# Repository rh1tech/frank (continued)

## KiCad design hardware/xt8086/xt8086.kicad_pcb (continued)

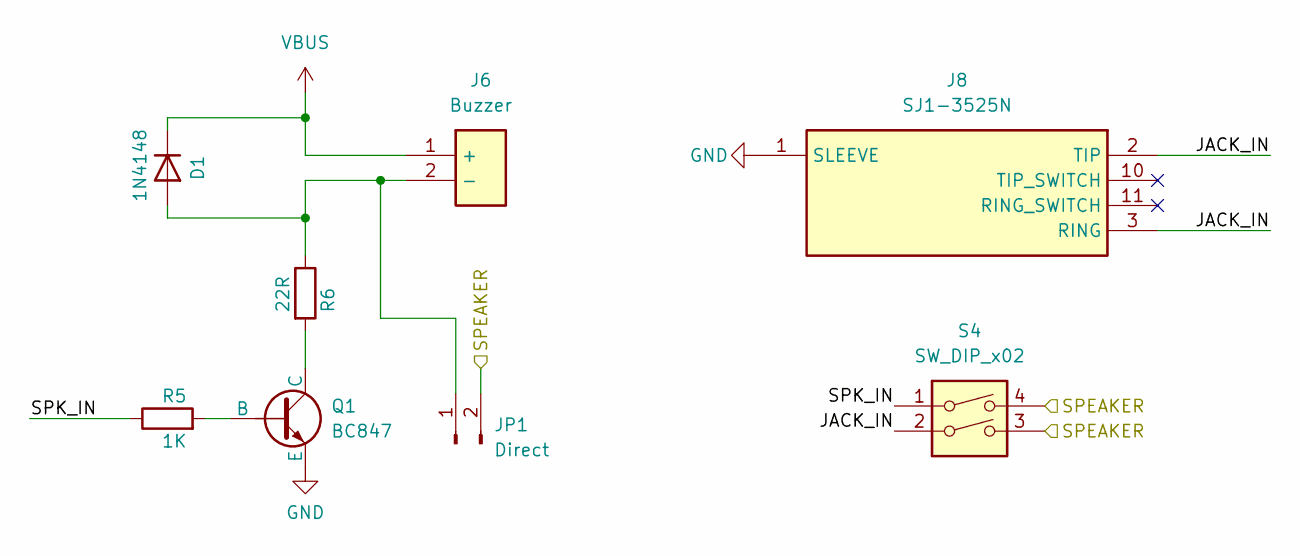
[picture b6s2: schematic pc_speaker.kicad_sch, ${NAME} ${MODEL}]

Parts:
D1: 1N4148; D_SOD-323
J6: Buzzer; Buzzer_12x8.5RM6.5; Mouser Part Number 490-CMT-7525-80SMTTR
J8: SJ1-3525N; AudioJack_3.5mm_SJ1-3525N; Mouser Part Number 490-SJ1-3525N
JP1: Direct; SolderJumper-2_P1.3mm_Open_Pad1.0x1.5mm
Q1: BC847; SOT-23
R5: 1K; R_0805_2012Metric
R6: 22R; R_0805_2012Metric
S4: SW_DIP_x02; SW_DIP_SPSTx02_Slide_9.78x7.26mm_W7.62mm_P2.54mm

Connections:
/Audio/JACK_IN: J8.2 (TIP), J8.3 (RING), S4.2
/Audio/SPEAKER: JP1.2, S4.3, S4.4; also elsewhere on the board
/Audio/SPK_IN: R5.1, S4.1
GND: J8.1 (SLEEVE), Q1.3 (E); also elsewhere on the board
unnamed: D1.2 (A), J6.2 (-), JP1.1, R6.1
unnamed: Q1.2 (B), R5.2
unnamed: Q1.1 (C), R6.2
VBUS: D1.1 (K), J6.1 (+); also elsewhere on the board

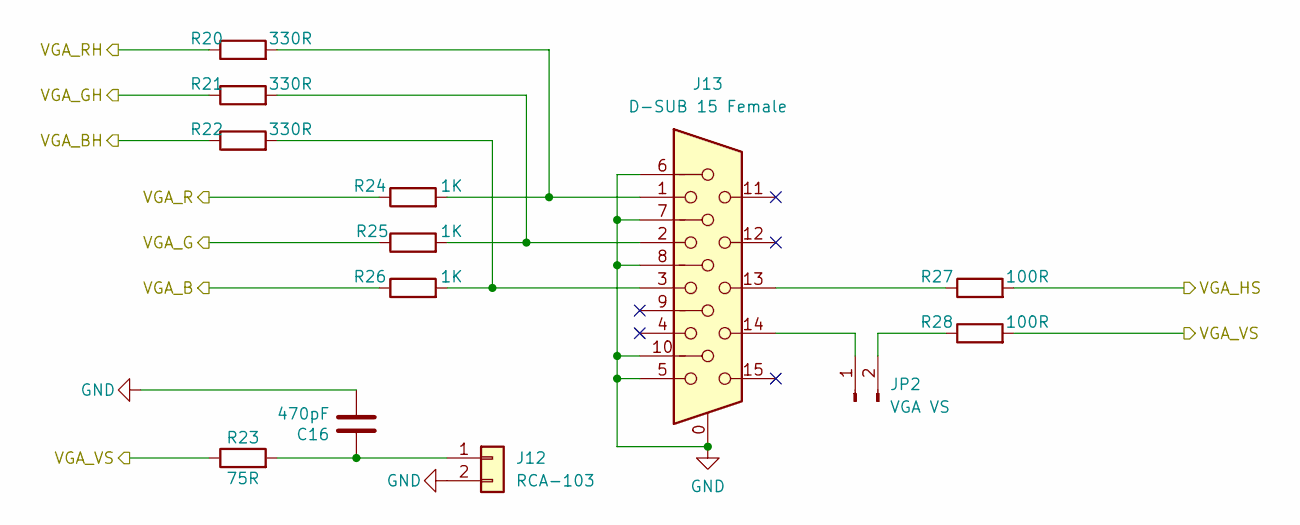
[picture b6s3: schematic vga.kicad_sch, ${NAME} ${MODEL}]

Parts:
C16: 470pF; C_0805_2012Metric
J12: RCA-103; BarrelJack_RCJ-012
J13: D-SUB 15 Female; DSUB-15_Female
JP2: VGA VS; PinHeader_1x02_P2.54mm
R20, R21, R22: 330R; R_0805_2012Metric
R23: 75R; R_0805_2012Metric
R24, R25, R26: 1K; R_0805_2012Metric
R27, R28: 100R; R_0805_2012Metric

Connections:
/PGA2350/GP30: R26.1; also elsewhere on the board
/PGA2350/GP31: R22.1; also elsewhere on the board
/PGA2350/GP32: R25.1; also elsewhere on the board
/PGA2350/GP33: R21.1; also elsewhere on the board
/PGA2350/GP34: R24.1; also elsewhere on the board
/PGA2350/GP35: R20.1; also elsewhere on the board
/PGA2350/GP36: R27.2; also elsewhere on the board
/PGA2350/GP37: R23.1, R28.2; also elsewhere on the board
GND: C16.2, J12.2, J13.0, J13.5, J13.6, J13.7, J13.8, J13.10; also elsewhere on the board
unnamed: C16.1, J12.1, R23.2
unnamed: J13.1, R20.2, R24.2
unnamed: J13.2, R21.2, R25.2
unnamed: J13.3, R22.2, R26.2
unnamed: J13.13, R27.1
unnamed: J13.14, JP2.1
unnamed: JP2.2, R28.1

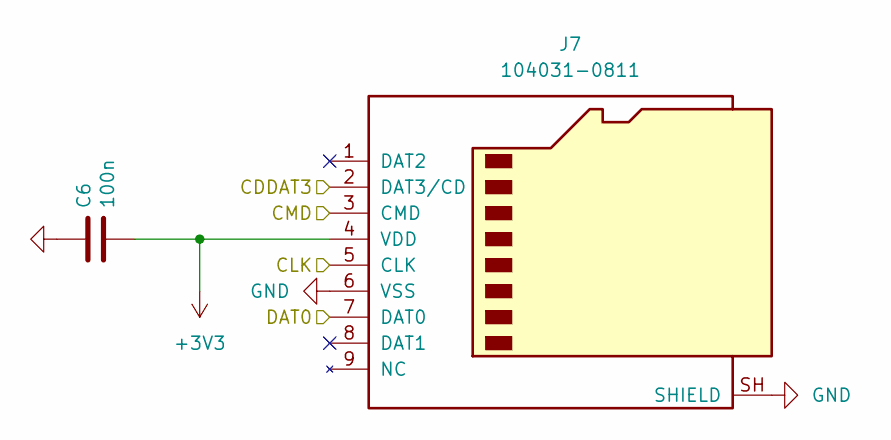
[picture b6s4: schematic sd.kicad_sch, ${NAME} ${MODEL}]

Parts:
C6: 100n; C_0805_2012Metric
J7: 104031-0811; MicroSD_SMD_Long

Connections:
+3V3: C6.2, J7.4 (VDD); also elsewhere on the board
/Micro SD/CDDAT3: J7.2 (DAT3/CD); also elsewhere on the board
/Micro SD/CLK: J7.5 (CLK); also elsewhere on the board
/Micro SD/CMD: J7.3 (CMD); also elsewhere on the board
/Micro SD/DAT0: J7.7 (DAT0); also elsewhere on the board
GND: C6.1, J7.6 (VSS), J7.SH (SHIELD); also elsewhere on the board

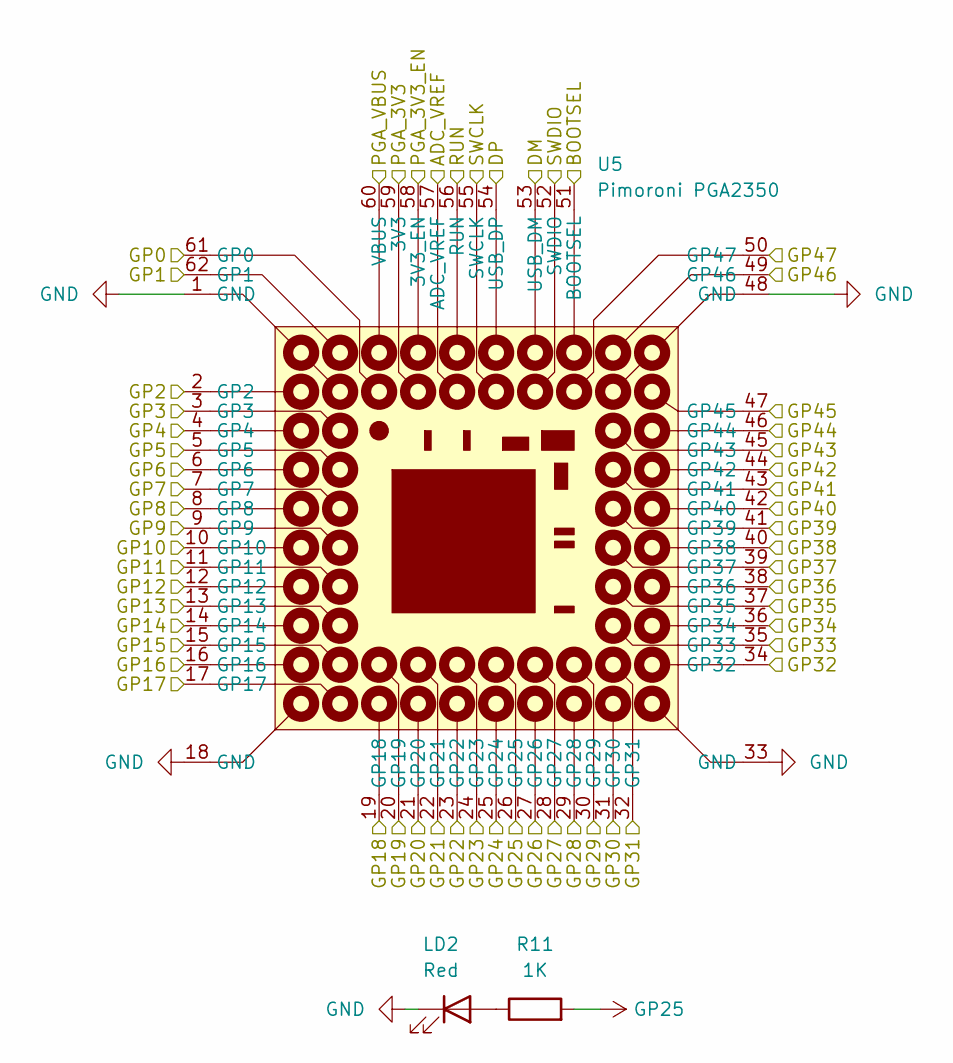
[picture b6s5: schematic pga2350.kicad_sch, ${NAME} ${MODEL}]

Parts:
LD2: Red; LED_0805_2012Metric_Pad1.15x1.40mm_HandSolder
R11: 1K; R_0805_2012Metric
U5: Pimoroni PGA2350; PGA2350

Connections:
+3V3: U5.59 (3V3); also elsewhere on the board
/A16/GP16: U5.16 (GP16); also elsewhere on the board
/A17/GP17: U5.17 (GP17); also elsewhere on the board
/A18/GP18: U5.19 (GP18); also elsewhere on the board
/A19/GP19: U5.20 (GP19); also elsewhere on the board
/AD0/GP0: U5.61 (GP0); also elsewhere on the board
/AD1/GP1: U5.62 (GP1); also elsewhere on the board
/AD2/GP2: U5.2 (GP2); also elsewhere on the board
/AD3/GP3: U5.3 (GP3); also elsewhere on the board
/AD4/GP4: U5.4 (GP4); also elsewhere on the board
/AD5/GP5: U5.5 (GP5); also elsewhere on the board
/AD6/GP6: U5.6 (GP6); also elsewhere on the board
/AD7/GP7: U5.7 (GP7); also elsewhere on the board
/AD8/GP8: U5.8 (GP8); also elsewhere on the board
/AD9/GP9: U5.9 (GP9); also elsewhere on the board
/AD10/GP10: U5.10 (GP10); also elsewhere on the board
/AD11/GP11: U5.11 (GP11); also elsewhere on the board
/AD12/GP12: U5.12 (GP12); also elsewhere on the board
/AD13/GP13: U5.13 (GP13); also elsewhere on the board
/AD14/GP14: U5.14 (GP14); also elsewhere on the board
/AD15/GP15: U5.15 (GP15); also elsewhere on the board
/ALE/GP20: U5.21 (GP20); also elsewhere on the board
/Audio/SPEAKER: U5.49 (GP46); also elsewhere on the board
/BOOTSEL: U5.51 (BOOTSEL); also elsewhere on the board
/CLK/GP29: U5.30 (GP29); also elsewhere on the board
/GP27: U5.28 (GP27); also elsewhere on the board
/INTA/GP23: U5.24 (GP23); also elsewhere on the board
/INTR/GP26: U5.27 (GP26); also elsewhere on the board
/MIO/GP24: U5.25 (GP24); also elsewhere on the board
/Micro SD/CDDAT3: U5.43 (GP41); also elsewhere on the board
/Micro SD/CLK: U5.44 (GP42); also elsewhere on the board
/Micro SD/CMD: U5.45 (GP43); also elsewhere on the board
/Micro SD/DAT0: U5.42 (GP40); also elsewhere on the board
/PGA2350/ADC_VREF: U5.57 (ADC_VREF)
/PGA2350/DM: U5.53 (USB_DM); also elsewhere on the board
/PGA2350/DP: U5.54 (USB_DP); also elsewhere on the board
/PGA2350/GP30: U5.31 (GP30); also elsewhere on the board
/PGA2350/GP31: U5.32 (GP31); also elsewhere on the board
/PGA2350/GP32: U5.34 (GP32); also elsewhere on the board
/PGA2350/GP33: U5.35 (GP33); also elsewhere on the board
/PGA2350/GP34: U5.36 (GP34); also elsewhere on the board
/PGA2350/GP35: U5.37 (GP35); also elsewhere on the board
/PGA2350/GP36: U5.38 (GP36); also elsewhere on the board
/PGA2350/GP37: U5.39 (GP37); also elsewhere on the board
/PGA2350/GP38: U5.40 (GP38)
/PGA2350/GP39: U5.41 (GP39)
/PGA2350/GP47: U5.50 (GP47)
/PGA2350/PGA_3V3_EN: U5.58 (3V3_EN)
/RD/GP21: U5.22 (GP21); also elsewhere on the board
/RESET/GP28: U5.29 (GP28); also elsewhere on the board
/RUN: U5.56 (RUN); also elsewhere on the board
/SWCLK: U5.55 (SWCLK); also elsewhere on the board
/SWDIO: U5.52 (SWDIO); also elsewhere on the board
/UART0_RX: U5.47 (GP45); also elsewhere on the board
/UART0_TX: U5.46 (GP44); also elsewhere on the board
/WR/GP22: U5.23 (GP22); also elsewhere on the board
GND: LD2.1 (K), U5.1 (GND), U5.18 (GND), U5.33 (GND), U5.48 (GND); also elsewhere on the board
GP25: R11.2, U5.26 (GP25); also elsewhere on the board
unnamed: LD2.2 (A), R11.1
VBUS: U5.60 (VBUS); also elsewhere on the board

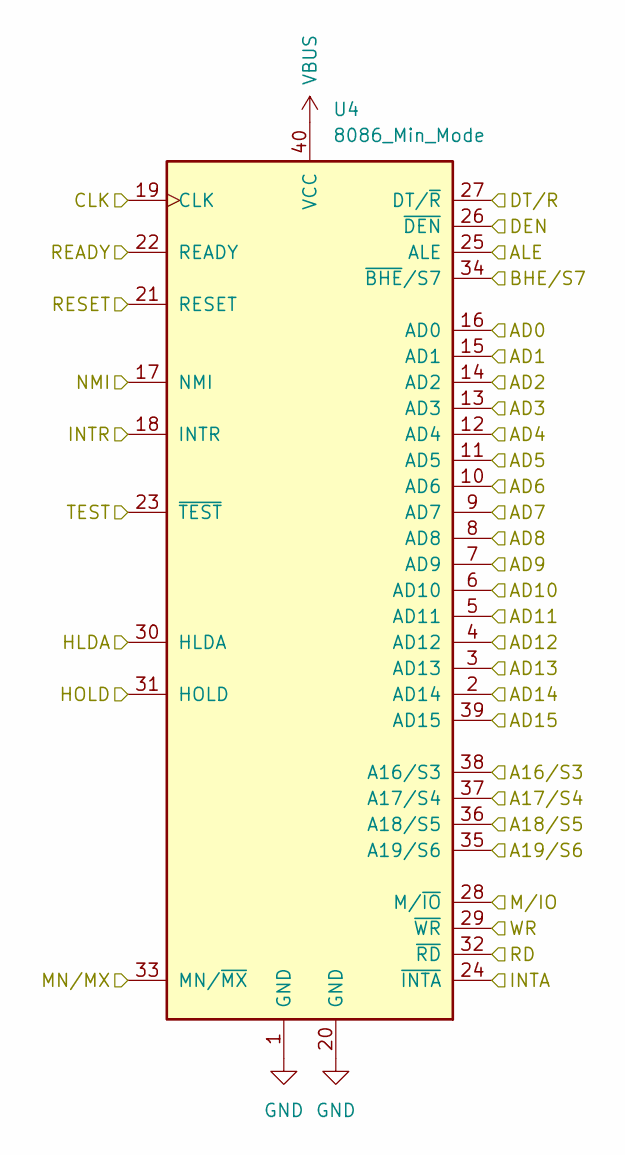
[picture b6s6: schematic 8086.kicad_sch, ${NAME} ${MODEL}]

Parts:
U4: 8086_Min_Mode; DIP-40_W15.24mm

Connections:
/A16/GP16: U4.38 (A16/S3); also elsewhere on the board
/A17/GP17: U4.37 (A17/S4); also elsewhere on the board
/A18/GP18: U4.36 (A18/S5); also elsewhere on the board
/A19/GP19: U4.35 (A19/S6); also elsewhere on the board
/AD0/GP0: U4.16 (AD0); also elsewhere on the board
/AD1/GP1: U4.15 (AD1); also elsewhere on the board
/AD2/GP2: U4.14 (AD2); also elsewhere on the board
/AD3/GP3: U4.13 (AD3); also elsewhere on the board
/AD4/GP4: U4.12 (AD4); also elsewhere on the board
/AD5/GP5: U4.11 (AD5); also elsewhere on the board
/AD6/GP6: U4.10 (AD6); also elsewhere on the board
/AD7/GP7: U4.9 (AD7); also elsewhere on the board
/AD8/GP8: U4.8 (AD8); also elsewhere on the board
/AD9/GP9: U4.7 (AD9); also elsewhere on the board
/AD10/GP10: U4.6 (AD10); also elsewhere on the board
/AD11/GP11: U4.5 (AD11); also elsewhere on the board
/AD12/GP12: U4.4 (AD12); also elsewhere on the board
/AD13/GP13: U4.3 (AD13); also elsewhere on the board
/AD14/GP14: U4.2 (AD14); also elsewhere on the board
/AD15/GP15: U4.39 (AD15); also elsewhere on the board
/ALE/GP20: U4.25 (ALE); also elsewhere on the board
/CLK/GP29: U4.19 (CLK); also elsewhere on the board
/DEN: U4.26 (~DEN); also elsewhere on the board
/DT/R: U4.27 (DT/~R); also elsewhere on the board
/HLDA: U4.30 (HLDA); also elsewhere on the board
/INTA/GP23: U4.24 (~INTA); also elsewhere on the board
/INTR/GP26: U4.18 (INTR); also elsewhere on the board
/MIO/GP24: U4.28 (M/~IO); also elsewhere on the board
/MN/MX: U4.33 (MN/~MX); also elsewhere on the board
/RD/GP21: U4.32 (~RD); also elsewhere on the board
/READY: U4.22 (READY); also elsewhere on the board
/RESET/GP28: U4.21 (RESET); also elsewhere on the board
/TEST: U4.23 (~TEST); also elsewhere on the board
/WR/GP22: U4.29 (~WR); also elsewhere on the board
GND: U4.1 (GND), U4.17 (NMI), U4.20 (GND), U4.31 (HOLD); also elsewhere on the board
GP25: U4.34 (~BHE/S7); also elsewhere on the board
VBUS: U4.40 (VCC); also elsewhere on the board

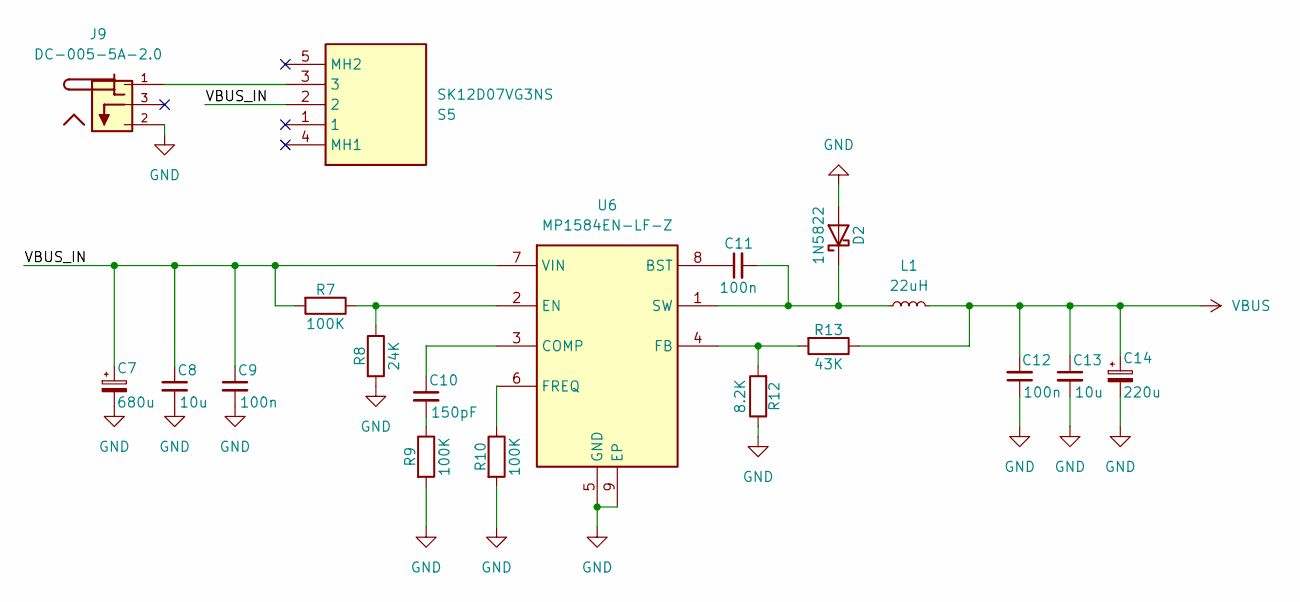
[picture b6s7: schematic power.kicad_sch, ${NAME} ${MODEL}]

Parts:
C7: 680u; C_Radial_D8.0mm_P3.50mm
C8, C13: 10u; C_0805_2012Metric
C9, C11, C12: 100n; C_0805_2012Metric
C10: 150pF; R_0805_2012Metric
C14: 220u; C_Radial_D6.3mm_P2.50mm
D2: 1N5822; D_SMA
J9: DC-005-5A-2.0; BarrelJack_DC-005; PARTREV A0
L1: 22uH; L_Radial_D9.5mm_P5.00mm_Fastron_07HVP
R7, R9, R10: 100K; R_0805_2012Metric
R8: 24K; R_0805_2012Metric
R12: 8.2K; R_0805_2012Metric
R13: 43K; R_0805_2012Metric
S5: SK12D07VG3NS; Switch_Slide_SK12D07VG3NS; Mouser Part Number 611-SK12D07VG3NS
U6: MP1584EN-LF-Z; SOIC-9_P1.27mm; Mouser Part Number 946-MP1584ENLFZ

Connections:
/Power/VBUS_IN: C7.1, C8.1, C9.1, R7.2, S5.2, U6.7 (VIN)
GND: C7.2, C8.2, C9.2, C12.1, C13.2, C14.2, D2.2 (A), J9.2, R8.2, R9.2, R10.2, R12.1, U6.5 (GND), U6.9 (EP); also elsewhere on the board
unnamed: C10.2, R9.1
unnamed: C11.2, D2.1 (K), L1.1, U6.1 (SW)
unnamed: J9.1, S5.3
unnamed: C11.1, U6.8 (BST)
unnamed: C10.1, U6.3 (COMP)
unnamed: R7.1, R8.1, U6.2 (EN)
unnamed: R12.2, R13.2, U6.4 (FB)
unnamed: R10.1, U6.6 (FREQ)
VBUS: C12.2, C13.1, C14.1, L1.2, R13.1; also elsewhere on the board

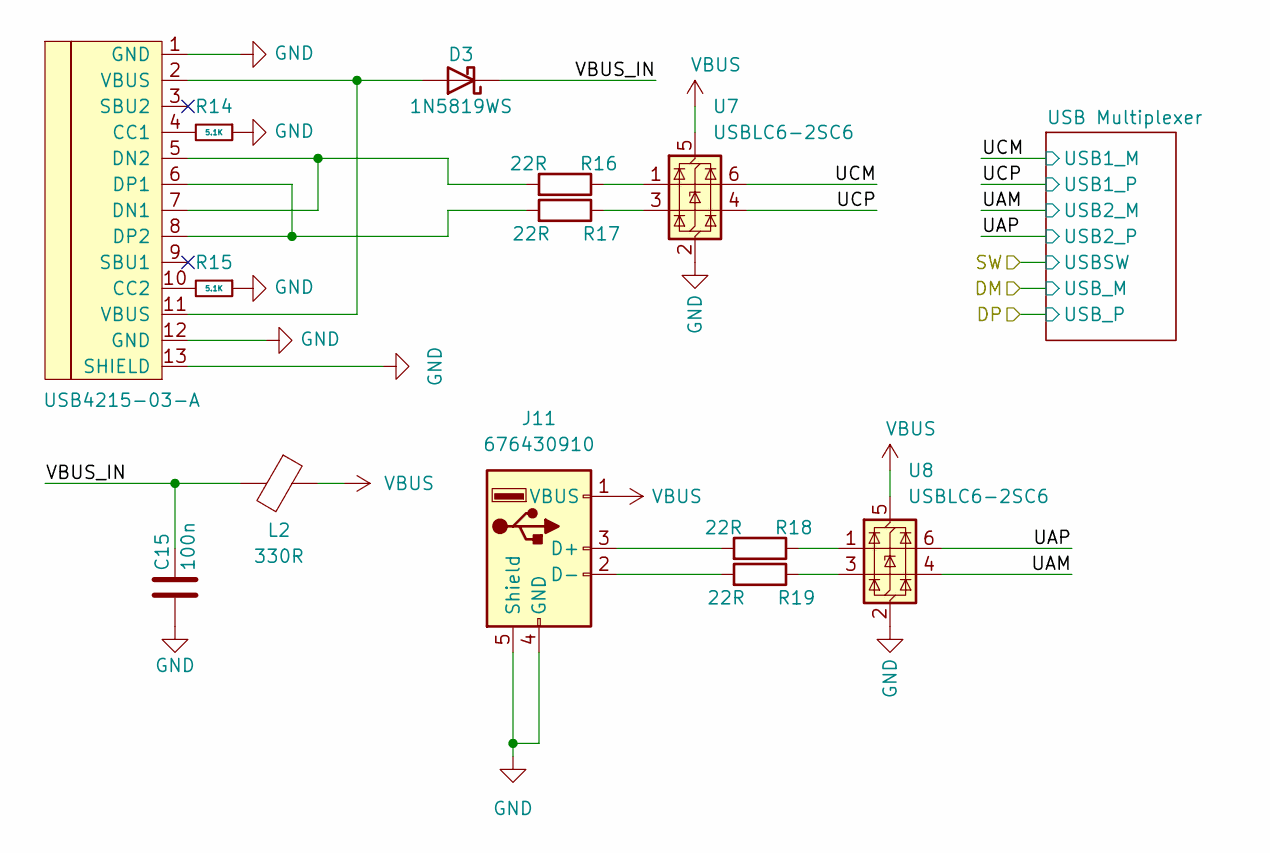
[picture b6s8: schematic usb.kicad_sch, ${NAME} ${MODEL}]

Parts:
C15: 100n; C_0805_2012Metric
D3: 1N5819WS; D_SOD-323
J10: USB4215-03-A; USB_C_Receptacle; LCSC C165948
J11: 676430910; USB_A_Single
L2: 330R; R_0805_2012Metric
R14, R15: 5.1K; R_0805_2012Metric
R16, R17, R18, R19: 22R; R_0805_2012Metric
U7, U8: USBLC6-2SC6; SOT-23-6

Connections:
/USB/UAM: U8.4 (I/O2); also elsewhere on the board
/USB/UAP: U8.6 (I/O1); also elsewhere on the board
/USB/UCM: U7.6 (I/O1); also elsewhere on the board
/USB/UCP: U7.4 (I/O2); also elsewhere on the board
/USB/VBUS_IN: C15.1, D3.1 (K), L2.2
GND: C15.2, J10.1 (GND), J10.12 (GND), J10.13 (SHIELD), J11.4 (GND), J11.5 (Shield), R14.1, R15.1, U7.2 (GND), U8.2 (GND); also elsewhere on the board
unnamed: D3.2 (A), J10.2 (VBUS), J10.11 (VBUS)
unnamed: J10.4 (CC1), R14.2
unnamed: J10.10 (CC2), R15.2
unnamed: J10.5 (DN2), J10.7 (DN1), R16.2
unnamed: J10.6 (DP1), J10.8 (DP2), R17.2
unnamed: J11.3 (D+), R18.2
unnamed: J11.2 (D-), R19.2
unnamed: R16.1, U7.1 (I/O1)
unnamed: R17.1, U7.3 (I/O2)
unnamed: R18.1, U8.1 (I/O1)
unnamed: R19.1, U8.3 (I/O2)
VBUS: J11.1 (VBUS), L2.1, U7.5 (VBUS), U8.5 (VBUS); also elsewhere on the board

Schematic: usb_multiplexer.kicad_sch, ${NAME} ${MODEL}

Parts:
C5: 100n; C_0805_2012Metric
R4: 10K; R_0805_2012Metric
U3: 74HC4052D; 74HC4052N; Mouser Part Number 771-74HC4052D-T

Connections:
/PGA2350/DM: U3.3 (2Z); also elsewhere on the board
/PGA2350/DP: U3.13 (1Z); also elsewhere on the board
/USB/SW: R4.2, U3.10 (S0); also elsewhere on the board
/USB/UAM: U3.5 (2Y1); also elsewhere on the board
/USB/UAP: U3.14 (1Y1); also elsewhere on the board
/USB/UCM: U3.1 (2Y0); also elsewhere on the board
/USB/UCP: U3.12 (1Y0); also elsewhere on the board
GND: C5.1, R4.1, U3.2 (2Y2), U3.4 (2Y3), U3.6 (~E), U3.7 (VEE), U3.8 (GND), U3.9 (S1), U3.11 (1Y3), U3.15 (1Y2); also elsewhere on the board
VBUS: C5.2, U3.16 (VCC); also elsewhere on the board

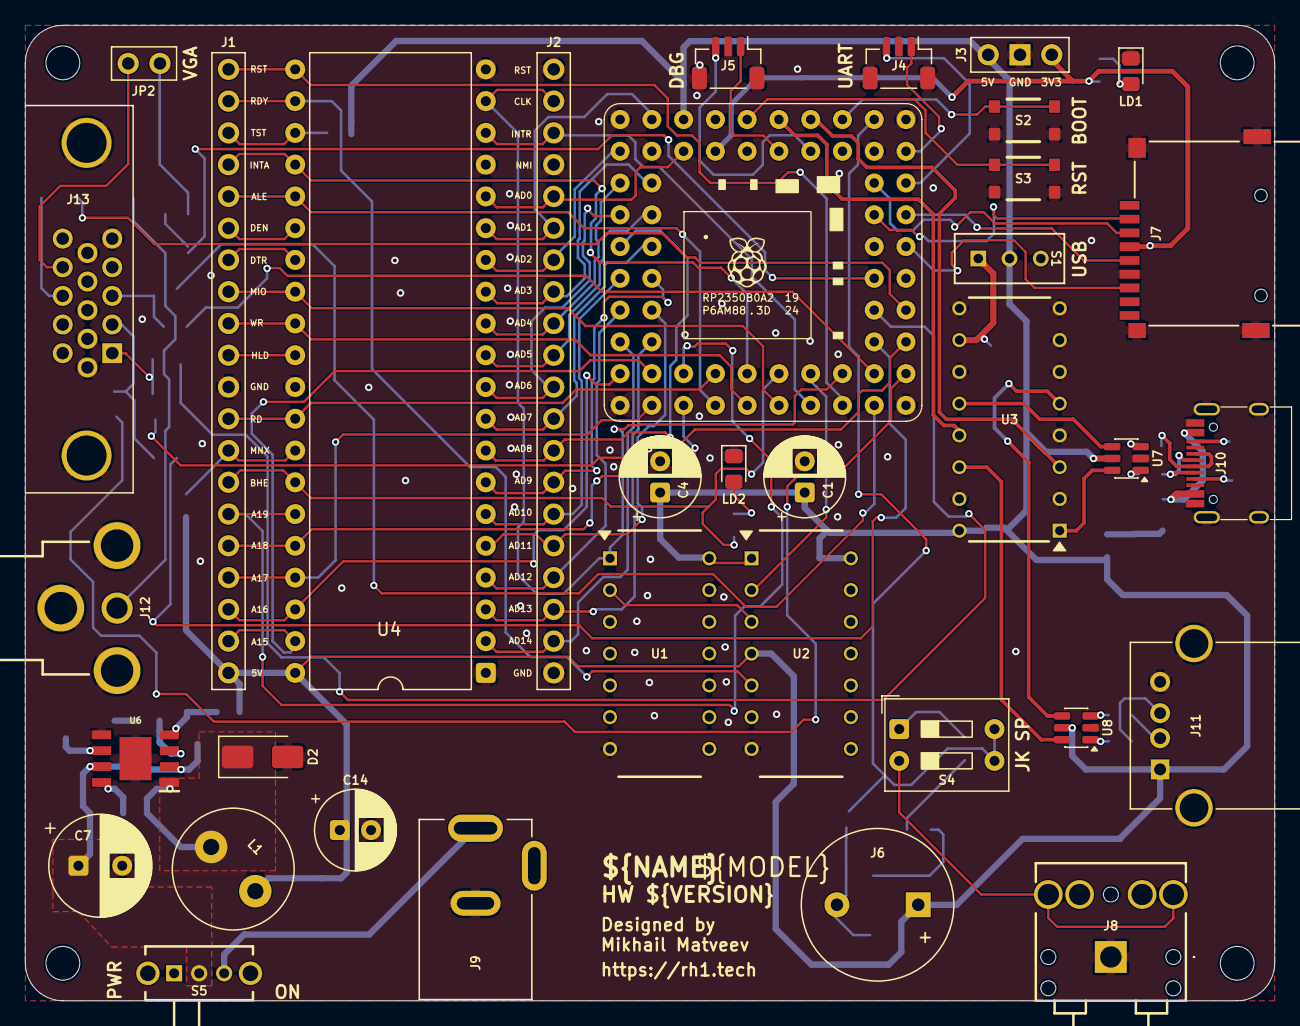
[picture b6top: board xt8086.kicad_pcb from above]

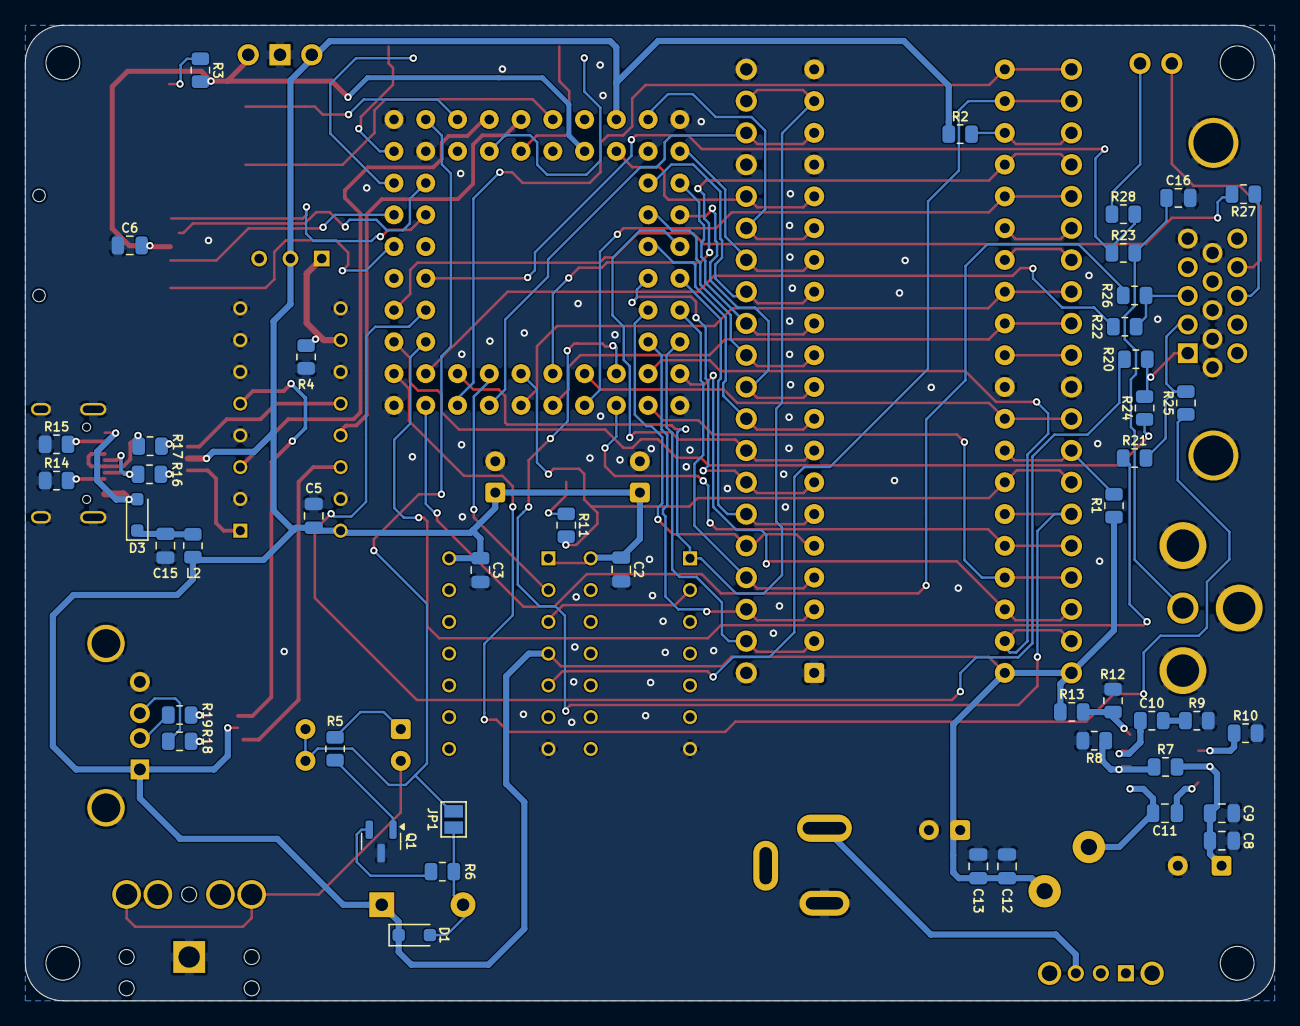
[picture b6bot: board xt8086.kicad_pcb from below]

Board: 2 copper layers, 99.9 x 78.0 mm, 84 parts (45 on the bottom side), 101 nets.
